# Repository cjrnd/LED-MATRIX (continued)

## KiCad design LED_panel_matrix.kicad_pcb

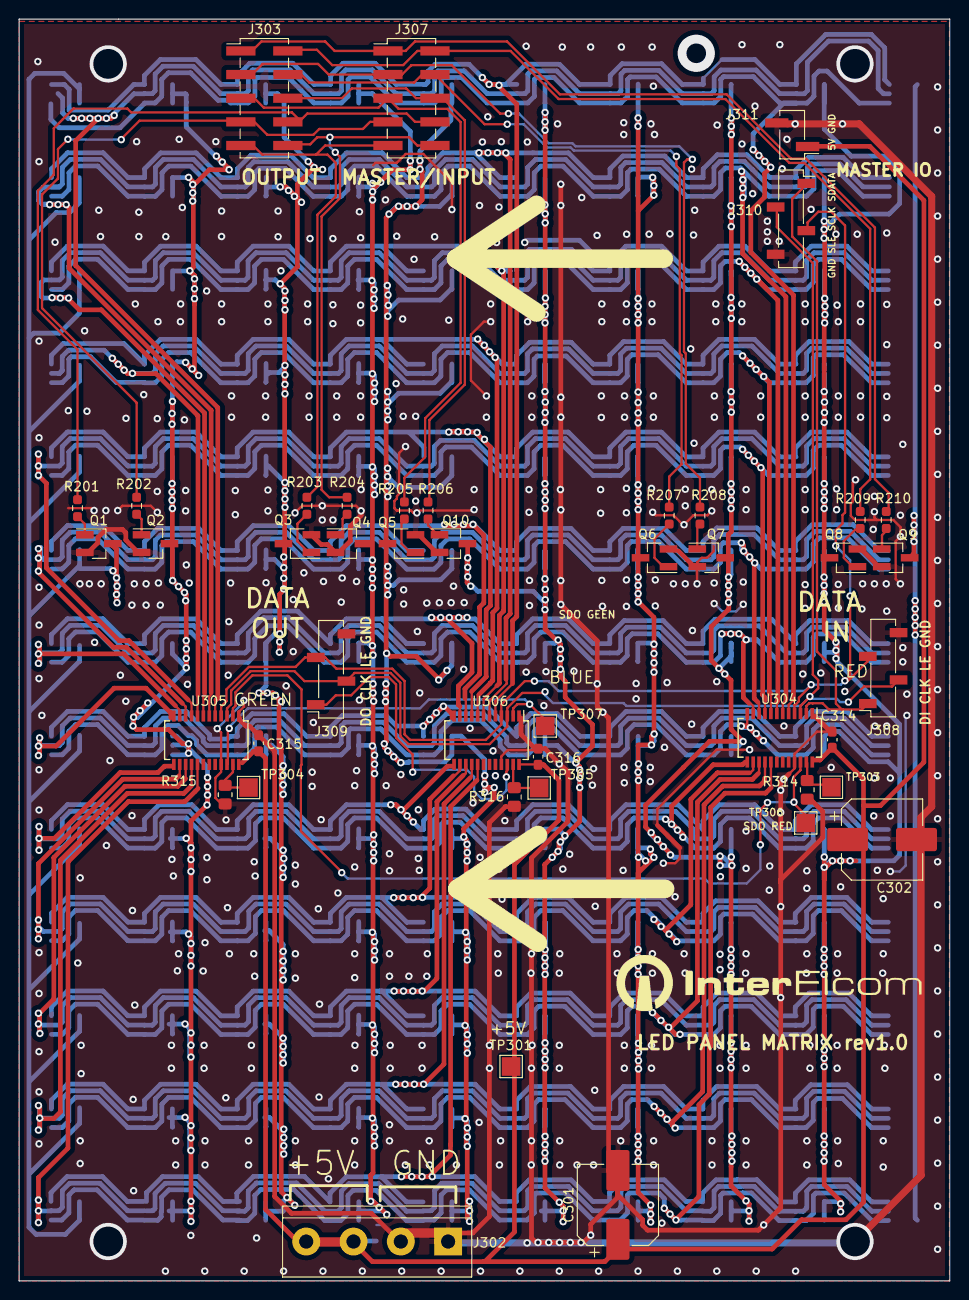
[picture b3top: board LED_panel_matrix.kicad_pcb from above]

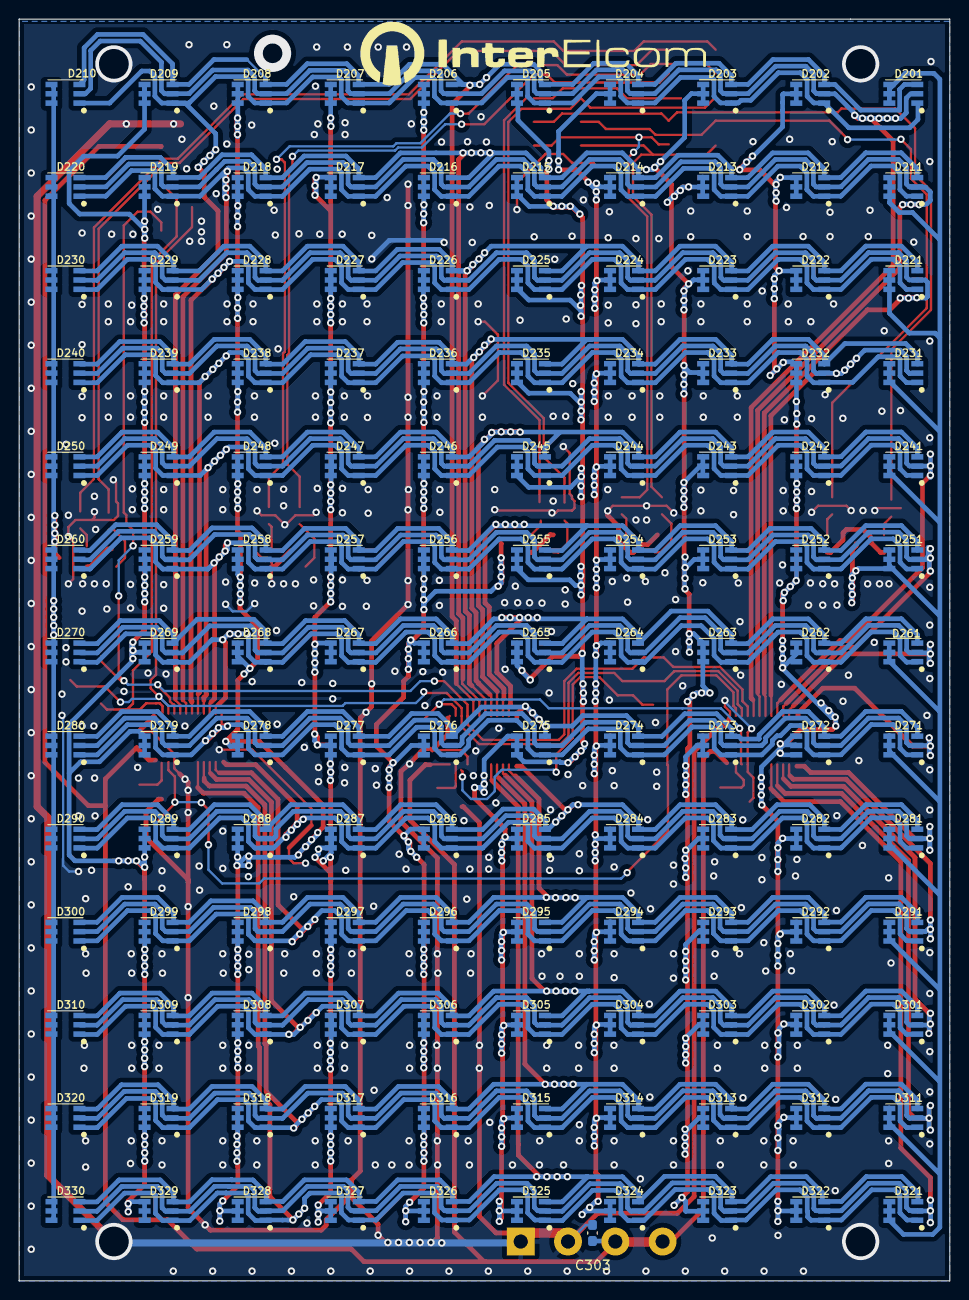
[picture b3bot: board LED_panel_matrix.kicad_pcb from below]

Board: 2 copper layers, 100.0 x 135.5 mm, 175 parts (131 on the bottom side), 80 nets.

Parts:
C301, C302: 220u; CP_Elec_8x10.5
C303, C314, C315, C316: 100n; C_0603_1608Metric_Pad1.08x0.95mm_HandSolder
D201, D202, D203, D204, D205, D206, D207, D208, D209, D210, D211, D212, D213, D214, D215, D216, D217, D218, D219, D220, D221, D222, D223, D224, D225, D226, D227, D228, D229, D230, D231, D232, D233, D234, D235, D236, D237, D238, D239, D240, D241, D242, D243, D244, D245, D246, D247, D248, D249, D250, D251, D252, D253, D254, D255, D256, D257, D258, D259, D260, D261, D262, D263, D264, D265, D266, D267, D268, D269, D270, D271, D272, D273, D274, D275, D276, D277, D278, D279, D280, D281, D282, D283, D284, D285, D286, D287, D288, D289, D290, D291, D292, D293, D294, D295, D296, D297, D298, D299, D300, D301, D302, D303, D304, D305, D306, D307, D308, D309, D310, D311, D312, D313, D314, D315, D316, D317, D318, D319, D320, D321, D322, D323, D324, D325, D326, D327, D328, D329, D330: LED_RGB; IE-3535RGB
J302: Power Input; TerminalBlock_bornier-4_P5.08mm
J303, J307: IDC10; PinHeader_2x05_P2.54mm_Vertical_SMD
J308: DATA INPUT; PinSocket_1x04_P2.54mm_Vertical_SMD_Pin1Right
J309: Data OUT; PinSocket_1x04_P2.54mm_Vertical_SMD_Pin1Right
J310: Serial_BUS; PinSocket_1x04_P2.54mm_Vertical_SMD_Pin1Right
J311: BOOT_TO/ SELECTOR; PinHeader_1x02_P2.54mm_Vertical_SMD_Pin1Left
Q1, Q2, Q3, Q4, Q5, Q6, Q7, Q8, Q9, Q10: PMV45EN2R; SOT-23_Handsoldering
R201, R202, R203, R204, R205, R206, R207, R208, R209, R210: 100; R_0603_1608Metric_Pad0.98x0.95mm_HandSolder
R314: R_red; R_0805_2012Metric_Pad1.20x1.40mm_HandSolder
R315: R_green; R_0805_2012Metric_Pad1.20x1.40mm_HandSolder
R316: R_blue; R_0805_2012Metric_Pad1.20x1.40mm_HandSolder
TP301, TP303, TP304, TP305, TP306, TP307: TestPoint; TestPoint_Pad_2.0x2.0mm
U304, U305, U306: SM16206; SSOP-24_3.9x8.7mm_P0.635mm

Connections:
+5V: C301.1, C302.1, C303.1, C314.1, C315.1, C316.1, J302.3, J302.4, J311.1, TP301.1, U304.24 (VDD), U305.24 (VDD), U306.24 (VDD)
/Logic/B_Row0: D201.4 (RA), D202.4 (RA), D203.4 (RA), D204.4 (RA), D205.4 (RA), D206.4 (RA), D207.4 (RA), D208.4 (RA), D209.4 (RA), D210.4 (RA), U306.5 (OUT0)
/Logic/B_Row1: D211.4 (RA), D212.4 (RA), D213.4 (RA), D214.4 (RA), D215.4 (RA), D216.4 (RA), D217.4 (RA), D218.4 (RA), D219.4 (RA), D220.4 (RA), U306.6 (OUT1)
/Logic/B_Row2: D221.4 (RA), D222.4 (RA), D223.4 (RA), D224.4 (RA), D225.4 (RA), D226.4 (RA), D227.4 (RA), D228.4 (RA), D229.4 (RA), D230.4 (RA), U306.7 (OUT2)
/Logic/B_Row3: D231.4 (RA), D232.4 (RA), D233.4 (RA), D234.4 (RA), D235.4 (RA), D236.4 (RA), D237.4 (RA), D238.4 (RA), D239.4 (RA), D240.4 (RA), U306.8 (OUT3)
/Logic/B_Row4: D241.4 (RA), D242.4 (RA), D243.4 (RA), D244.4 (RA), D245.4 (RA), D246.4 (RA), D247.4 (RA), D248.4 (RA), D249.4 (RA), D250.4 (RA), U306.9 (OUT4)
/Logic/B_Row5: D251.4 (RA), D252.4 (RA), D253.4 (RA), D254.4 (RA), D255.4 (RA), D256.4 (RA), D257.4 (RA), D258.4 (RA), D259.4 (RA), D260.4 (RA), U306.10 (OUT5)
/Logic/B_Row6: D261.4 (RA), D262.4 (RA), D263.4 (RA), D264.4 (RA), D265.4 (RA), D266.4 (RA), D267.4 (RA), D268.4 (RA), D269.4 (RA), D270.4 (RA), U306.11 (OUT6)
/Logic/B_Row7: D271.4 (RA), D272.4 (RA), D273.4 (RA), D274.4 (RA), D275.4 (RA), D276.4 (RA), D277.4 (RA), D278.4 (RA), D279.4 (RA), D280.4 (RA), U306.12 (OUT7)
/Logic/B_Row8: D281.4 (RA), D282.4 (RA), D283.4 (RA), D284.4 (RA), D285.4 (RA), D286.4 (RA), D287.4 (RA), D288.4 (RA), D289.4 (RA), D290.4 (RA), U306.13 (OUT8)
/Logic/B_Row9: D291.4 (RA), D292.4 (RA), D293.4 (RA), D294.4 (RA), D295.4 (RA), D296.4 (RA), D297.4 (RA), D298.4 (RA), D299.4 (RA), D300.4 (RA), U306.14 (OUT9)
/Logic/B_Row10: D301.4 (RA), D302.4 (RA), D303.4 (RA), D304.4 (RA), D305.4 (RA), D306.4 (RA), D307.4 (RA), D308.4 (RA), D309.4 (RA), D310.4 (RA), U306.15 (OUT10)
/Logic/B_Row11: D311.4 (RA), D312.4 (RA), D313.4 (RA), D314.4 (RA), D315.4 (RA), D316.4 (RA), D317.4 (RA), D318.4 (RA), D319.4 (RA), D320.4 (RA), U306.16 (OUT11)
/Logic/B_Row12: D321.4 (RA), D322.4 (RA), D323.4 (RA), D324.4 (RA), D325.4 (RA), D326.4 (RA), D327.4 (RA), D328.4 (RA), D329.4 (RA), D330.4 (RA), U306.17 (OUT12)
/Logic/Col0: J303.8, J307.8, R201.1
/Logic/Col1: J303.7, J307.7, R202.1
/Logic/Col2: J303.9, J307.9, R203.1
/Logic/Col3: J303.10, J307.10, R204.1
/Logic/Col4: J303.5, J307.5, R205.1
/Logic/Col5: J303.6, J307.6, R206.1
/Logic/Col6: J303.4, J307.4, R207.1
/Logic/Col7: J303.3, J307.3, R208.1
/Logic/Col8: J303.2, J307.2, R209.2
/Logic/Col9: J303.1, J307.1, R210.2
/Logic/G_Row0: D201.5 (GA), D202.5 (GA), D203.5 (GA), D204.5 (GA), D205.5 (GA), D206.5 (GA), D207.5 (GA), D208.5 (GA), D209.5 (GA), D210.5 (GA), U305.5 (OUT0)
/Logic/G_Row1: D211.5 (GA), D212.5 (GA), D213.5 (GA), D214.5 (GA), D215.5 (GA), D216.5 (GA), D217.5 (GA), D218.5 (GA), D219.5 (GA), D220.5 (GA), U305.6 (OUT1)
/Logic/G_Row2: D221.5 (GA), D222.5 (GA), D223.5 (GA), D224.5 (GA), D225.5 (GA), D226.5 (GA), D227.5 (GA), D228.5 (GA), D229.5 (GA), D230.5 (GA), U305.7 (OUT2)
/Logic/G_Row3: D231.5 (GA), D232.5 (GA), D233.5 (GA), D234.5 (GA), D235.5 (GA), D236.5 (GA), D237.5 (GA), D238.5 (GA), D239.5 (GA), D240.5 (GA), U305.8 (OUT3)
/Logic/G_Row4: D241.5 (GA), D242.5 (GA), D243.5 (GA), D244.5 (GA), D245.5 (GA), D246.5 (GA), D247.5 (GA), D248.5 (GA), D249.5 (GA), D250.5 (GA), U305.9 (OUT4)
/Logic/G_Row5: D251.5 (GA), D252.5 (GA), D253.5 (GA), D254.5 (GA), D255.5 (GA), D256.5 (GA), D257.5 (GA), D258.5 (GA), D259.5 (GA), D260.5 (GA), U305.10 (OUT5)
/Logic/G_Row6: D261.5 (GA), D262.5 (GA), D263.5 (GA), D264.5 (GA), D265.5 (GA), D266.5 (GA), D267.5 (GA), D268.5 (GA), D269.5 (GA), D270.5 (GA), U305.11 (OUT6)
/Logic/G_Row7: D271.5 (GA), D272.5 (GA), D273.5 (GA), D274.5 (GA), D275.5 (GA), D276.5 (GA), D277.5 (GA), D278.5 (GA), D279.5 (GA), D280.5 (GA), U305.12 (OUT7)
/Logic/G_Row8: D281.5 (GA), D282.5 (GA), D283.5 (GA), D284.5 (GA), D285.5 (GA), D286.5 (GA), D287.5 (GA), D288.5 (GA), D289.5 (GA), D290.5 (GA), U305.13 (OUT8)
/Logic/G_Row9: D291.5 (GA), D292.5 (GA), D293.5 (GA), D294.5 (GA), D295.5 (GA), D296.5 (GA), D297.5 (GA), D298.5 (GA), D299.5 (GA), D300.5 (GA), U305.14 (OUT9)
/Logic/G_Row10: D301.5 (GA), D302.5 (GA), D303.5 (GA), D304.5 (GA), D305.5 (GA), D306.5 (GA), D307.5 (GA), D308.5 (GA), D309.5 (GA), D310.5 (GA), U305.15 (OUT10)
/Logic/G_Row11: D311.5 (GA), D312.5 (GA), D313.5 (GA), D314.5 (GA), D315.5 (GA), D316.5 (GA), D317.5 (GA), D318.5 (GA), D319.5 (GA), D320.5 (GA), U305.16 (OUT11)
/Logic/G_Row12: D321.5 (GA), D322.5 (GA), D323.5 (GA), D324.5 (GA), D325.5 (GA), D326.5 (GA), D327.5 (GA), D328.5 (GA), D329.5 (GA), D330.5 (GA), U305.17 (OUT12)
/Logic/R_Bset: R316.1, TP305.1, U306.23 (R-EXT)
/Logic/R_Gset: R315.1, TP304.1, U305.23 (R-EXT)
/Logic/R_Row0: D201.6 (BA), D202.6 (BA), D203.6 (BA), D204.6 (BA), D205.6 (BA), D206.6 (BA), D207.6 (BA), D208.6 (BA), D209.6 (BA), D210.6 (BA), U304.5 (OUT0)
/Logic/R_Row1: D211.6 (BA), D212.6 (BA), D213.6 (BA), D214.6 (BA), D215.6 (BA), D216.6 (BA), D217.6 (BA), D218.6 (BA), D219.6 (BA), D220.6 (BA), U304.6 (OUT1)
/Logic/R_Row2: D221.6 (BA), D222.6 (BA), D223.6 (BA), D224.6 (BA), D225.6 (BA), D226.6 (BA), D227.6 (BA), D228.6 (BA), D229.6 (BA), D230.6 (BA), U304.7 (OUT2)
/Logic/R_Row3: D231.6 (BA), D232.6 (BA), D233.6 (BA), D234.6 (BA), D235.6 (BA), D236.6 (BA), D237.6 (BA), D238.6 (BA), D239.6 (BA), D240.6 (BA), U304.8 (OUT3)
/Logic/R_Row4: D241.6 (BA), D242.6 (BA), D243.6 (BA), D244.6 (BA), D245.6 (BA), D246.6 (BA), D247.6 (BA), D248.6 (BA), D249.6 (BA), D250.6 (BA), U304.9 (OUT4)
/Logic/R_Row5: D251.6 (BA), D252.6 (BA), D253.6 (BA), D254.6 (BA), D255.6 (BA), D256.6 (BA), D257.6 (BA), D258.6 (BA), D259.6 (BA), D260.6 (BA), U304.10 (OUT5)
/Logic/R_Row6: D261.6 (BA), D262.6 (BA), D263.6 (BA), D264.6 (BA), D265.6 (BA), D266.6 (BA), D267.6 (BA), D268.6 (BA), D269.6 (BA), D270.6 (BA), U304.11 (OUT6)
/Logic/R_Row7: D271.6 (BA), D272.6 (BA), D273.6 (BA), D274.6 (BA), D275.6 (BA), D276.6 (BA), D277.6 (BA), D278.6 (BA), D279.6 (BA), D280.6 (BA), U304.12 (OUT7)
/Logic/R_Row8: D281.6 (BA), D282.6 (BA), D283.6 (BA), D284.6 (BA), D285.6 (BA), D286.6 (BA), D287.6 (BA), D288.6 (BA), D289.6 (BA), D290.6 (BA), U304.13 (OUT8)
/Logic/R_Row9: D291.6 (BA), D292.6 (BA), D293.6 (BA), D294.6 (BA), D295.6 (BA), D296.6 (BA), D297.6 (BA), D298.6 (BA), D299.6 (BA), D300.6 (BA), U304.14 (OUT9)
/Logic/R_Row10: D301.6 (BA), D302.6 (BA), D303.6 (BA), D304.6 (BA), D305.6 (BA), D306.6 (BA), D307.6 (BA), D308.6 (BA), D309.6 (BA), D310.6 (BA), U304.15 (OUT10)
/Logic/R_Row11: D311.6 (BA), D312.6 (BA), D313.6 (BA), D314.6 (BA), D315.6 (BA), D316.6 (BA), D317.6 (BA), D318.6 (BA), D319.6 (BA), D320.6 (BA), U304.16 (OUT11)
/Logic/R_Row12: D321.6 (BA), D322.6 (BA), D323.6 (BA), D324.6 (BA), D325.6 (BA), D326.6 (BA), D327.6 (BA), D328.6 (BA), D329.6 (BA), D330.6 (BA), U304.17 (OUT12)
/Logic/R_Rset: R314.1, TP303.1, U304.23 (R-EXT)
GNDD: C301.2, C302.2, C303.2, C314.2, C315.2, C316.2, J302.1, J302.2, J308.4, J309.4, J310.4, J311.2, Q1.2 (S), Q2.2 (S), Q3.2 (S), Q4.2 (S), Q5.2 (S), Q6.2 (S), Q7.2 (S), Q8.2 (S), Q9.2 (S), Q10.2 (S), R314.2, R315.2, R316.2, U304.1 (GND), U304.21 (~OE), U305.1 (GND), U305.21 (~OE), U306.1 (GND), U306.21 (~OE)
unnamed: D201.1 (RK), D201.2 (GK), D201.3 (BK), D211.1 (RK), D211.2 (GK), D211.3 (BK), D221.1 (RK), D221.2 (GK), D221.3 (BK), D231.1 (RK), D231.2 (GK), D231.3 (BK), D241.1 (RK), D241.2 (GK), D241.3 (BK), D251.1 (RK), D251.2 (GK), D251.3 (BK), D261.1 (RK), D261.2 (GK), D261.3 (BK), D271.1 (RK), D271.2 (GK), D271.3 (BK), D281.1 (RK), D281.2 (GK), D281.3 (BK), D291.1 (RK), D291.2 (GK), D291.3 (BK), D301.1 (RK), D301.2 (GK), D301.3 (BK), D311.1 (RK), D311.2 (GK), D311.3 (BK), D321.1 (RK), D321.2 (GK), D321.3 (BK), Q1.3 (D)
unnamed: D202.1 (RK), D202.2 (GK), D202.3 (BK), D212.1 (RK), D212.2 (GK), D212.3 (BK), D222.1 (RK), D222.2 (GK), D222.3 (BK), D232.1 (RK), D232.2 (GK), D232.3 (BK), D242.1 (RK), D242.2 (GK), D242.3 (BK), D252.1 (RK), D252.2 (GK), D252.3 (BK), D262.1 (RK), D262.2 (GK), D262.3 (BK), D272.1 (RK), D272.2 (GK), D272.3 (BK), D282.1 (RK), D282.2 (GK), D282.3 (BK), D292.1 (RK), D292.2 (GK), D292.3 (BK), D302.1 (RK), D302.2 (GK), D302.3 (BK), D312.1 (RK), D312.2 (GK), D312.3 (BK), D322.1 (RK), D322.2 (GK), D322.3 (BK), Q2.3 (D)
unnamed: D203.1 (RK), D203.2 (GK), D203.3 (BK), D213.1 (RK), D213.2 (GK), D213.3 (BK), D223.1 (RK), D223.2 (GK), D223.3 (BK), D233.1 (RK), D233.2 (GK), D233.3 (BK), D243.1 (RK), D243.2 (GK), D243.3 (BK), D253.1 (RK), D253.2 (GK), D253.3 (BK), D263.1 (RK), D263.2 (GK), D263.3 (BK), D273.1 (RK), D273.2 (GK), D273.3 (BK), D283.1 (RK), D283.2 (GK), D283.3 (BK), D293.1 (RK), D293.2 (GK), D293.3 (BK), D303.1 (RK), D303.2 (GK), D303.3 (BK), D313.1 (RK), D313.2 (GK), D313.3 (BK), D323.1 (RK), D323.2 (GK), D323.3 (BK), Q3.3 (D)
unnamed: D204.1 (RK), D204.2 (GK), D204.3 (BK), D214.1 (RK), D214.2 (GK), D214.3 (BK), D224.1 (RK), D224.2 (GK), D224.3 (BK), D234.1 (RK), D234.2 (GK), D234.3 (BK), D244.1 (RK), D244.2 (GK), D244.3 (BK), D254.1 (RK), D254.2 (GK), D254.3 (BK), D264.1 (RK), D264.2 (GK), D264.3 (BK), D274.1 (RK), D274.2 (GK), D274.3 (BK), D284.1 (RK), D284.2 (GK), D284.3 (BK), D294.1 (RK), D294.2 (GK), D294.3 (BK), D304.1 (RK), D304.2 (GK), D304.3 (BK), D314.1 (RK), D314.2 (GK), D314.3 (BK), D324.1 (RK), D324.2 (GK), D324.3 (BK), Q4.3 (D)
unnamed: D205.1 (RK), D205.2 (GK), D205.3 (BK), D215.1 (RK), D215.2 (GK), D215.3 (BK), D225.1 (RK), D225.2 (GK), D225.3 (BK), D235.1 (RK), D235.2 (GK), D235.3 (BK), D245.1 (RK), D245.2 (GK), D245.3 (BK), D255.1 (RK), D255.2 (GK), D255.3 (BK), D265.1 (RK), D265.2 (GK), D265.3 (BK), D275.1 (RK), D275.2 (GK), D275.3 (BK), D285.1 (RK), D285.2 (GK), D285.3 (BK), D295.1 (RK), D295.2 (GK), D295.3 (BK), D305.1 (RK), D305.2 (GK), D305.3 (BK), D315.1 (RK), D315.2 (GK), D315.3 (BK), D325.1 (RK), D325.2 (GK), D325.3 (BK), Q5.3 (D)
unnamed: D206.1 (RK), D206.2 (GK), D206.3 (BK), D216.1 (RK), D216.2 (GK), D216.3 (BK), D226.1 (RK), D226.2 (GK), D226.3 (BK), D236.1 (RK), D236.2 (GK), D236.3 (BK), D246.1 (RK), D246.2 (GK), D246.3 (BK), D256.1 (RK), D256.2 (GK), D256.3 (BK), D266.1 (RK), D266.2 (GK), D266.3 (BK), D276.1 (RK), D276.2 (GK), D276.3 (BK), D286.1 (RK), D286.2 (GK), D286.3 (BK), D296.1 (RK), D296.2 (GK), D296.3 (BK), D306.1 (RK), D306.2 (GK), D306.3 (BK), D316.1 (RK), D316.2 (GK), D316.3 (BK), D326.1 (RK), D326.2 (GK), D326.3 (BK), Q10.3 (D)
unnamed: D207.1 (RK), D207.2 (GK), D207.3 (BK), D217.1 (RK), D217.2 (GK), D217.3 (BK), D227.1 (RK), D227.2 (GK), D227.3 (BK), D237.1 (RK), D237.2 (GK), D237.3 (BK), D247.1 (RK), D247.2 (GK), D247.3 (BK), D257.1 (RK), D257.2 (GK), D257.3 (BK), D267.1 (RK), D267.2 (GK), D267.3 (BK), D277.1 (RK), D277.2 (GK), D277.3 (BK), D287.1 (RK), D287.2 (GK), D287.3 (BK), D297.1 (RK), D297.2 (GK), D297.3 (BK), D307.1 (RK), D307.2 (GK), D307.3 (BK), D317.1 (RK), D317.2 (GK), D317.3 (BK), D327.1 (RK), D327.2 (GK), D327.3 (BK), Q6.3 (D)
unnamed: D208.1 (RK), D208.2 (GK), D208.3 (BK), D218.1 (RK), D218.2 (GK), D218.3 (BK), D228.1 (RK), D228.2 (GK), D228.3 (BK), D238.1 (RK), D238.2 (GK), D238.3 (BK), D248.1 (RK), D248.2 (GK), D248.3 (BK), D258.1 (RK), D258.2 (GK), D258.3 (BK), D268.1 (RK), D268.2 (GK), D268.3 (BK), D278.1 (RK), D278.2 (GK), D278.3 (BK), D288.1 (RK), D288.2 (GK), D288.3 (BK), D298.1 (RK), D298.2 (GK), D298.3 (BK), D308.1 (RK), D308.2 (GK), D308.3 (BK), D318.1 (RK), D318.2 (GK), D318.3 (BK), D328.1 (RK), D328.2 (GK), D328.3 (BK), Q7.3 (D)
unnamed: D209.1 (RK), D209.2 (GK), D209.3 (BK), D219.1 (RK), D219.2 (GK), D219.3 (BK), D229.1 (RK), D229.2 (GK), D229.3 (BK), D239.1 (RK), D239.2 (GK), D239.3 (BK), D249.1 (RK), D249.2 (GK), D249.3 (BK), D259.1 (RK), D259.2 (GK), D259.3 (BK), D269.1 (RK), D269.2 (GK), D269.3 (BK), D279.1 (RK), D279.2 (GK), D279.3 (BK), D289.1 (RK), D289.2 (GK), D289.3 (BK), D299.1 (RK), D299.2 (GK), D299.3 (BK), D309.1 (RK), D309.2 (GK), D309.3 (BK), D319.1 (RK), D319.2 (GK), D319.3 (BK), D329.1 (RK), D329.2 (GK), D329.3 (BK), Q8.3 (D)
unnamed: D210.1 (RK), D210.2 (GK), D210.3 (BK), D220.1 (RK), D220.2 (GK), D220.3 (BK), D230.1 (RK), D230.2 (GK), D230.3 (BK), D240.1 (RK), D240.2 (GK), D240.3 (BK), D250.1 (RK), D250.2 (GK), D250.3 (BK), D260.1 (RK), D260.2 (GK), D260.3 (BK), D270.1 (RK), D270.2 (GK), D270.3 (BK), D280.1 (RK), D280.2 (GK), D280.3 (BK), D290.1 (RK), D290.2 (GK), D290.3 (BK), D300.1 (RK), D300.2 (GK), D300.3 (BK), D310.1 (RK), D310.2 (GK), D310.3 (BK), D320.1 (RK), D320.2 (GK), D320.3 (BK), D330.1 (RK), D330.2 (GK), D330.3 (BK), Q9.3 (D)
unnamed: Q1.1 (G), R201.2
unnamed: Q2.1 (G), R202.2
unnamed: Q3.1 (G), R203.2
unnamed: Q4.1 (G), R204.2
unnamed: Q5.1 (G), R205.2
unnamed: Q10.1 (G), R206.2
unnamed: Q6.1 (G), R207.2
unnamed: Q7.1 (G), R208.2
unnamed: Q8.1 (G), R209.1
unnamed: Q9.1 (G), R210.1
unnamed: TP306.1, U304.22 (SDO), U305.2 (SDI)
unnamed: TP307.1, U305.22 (SDO), U306.2 (SDI)
SDO: J309.1, U306.22 (SDO)
S_CLK: J308.2, J309.2, J310.2, U304.3 (CLK), U305.3 (CLK), U306.3 (CLK)
S_DATA: J308.1, J310.1, U304.2 (SDI)
S_LE: J308.3, J309.3, J310.3, U304.4 (LE), U305.4 (LE), U306.4 (LE)

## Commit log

2023-04-13 added library
2023-04-13 library
    kk
2023-04-13 Revert "as"
    This reverts commit 9888ac46315cec0378cb4dbfa218d1b207e4798e.
2023-04-16 matrix done
2023-04-16 Fixed GND planes and rerouted bottom layer signals
2023-04-20 finished schematic of daughter board
2023-04-26 time is just a number
2023-04-27 PCB doughter - layout
2023-05-06 doughter PCB - with no GND connection
2023-05-07 Modified layout, filled GND planes, added info on silkscreen
2023-05-10 Changed all vias to through and modified whole layout
2023-05-10 finished pcb, except copper slab
2023-05-10 deleted zip file
2023-05-10 Minor fixes for doughterboard and added backup zips for mother
2023-05-10 added backup zips for mother
2023-05-10 added mounting holes,text on silk,fidducial markers,adjusted size of board
